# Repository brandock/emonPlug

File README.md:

# emonPlug Overview
OpenEnergyMonitor-compatible energy monitoring US plug. 

emonPlug is an energy monitoring transmitter unit that can monitor AC electrical consumption of one appliance connected to its NEMA 5-15R receptacle. 

emonPlug is designed to be used together with an emonBase web-connected base station from OpenEnergyMonitor. It can be thought of as an emonTx+emonVs for monitoring one appliance.

Make sure to read the warning and disclaimer below before starting any work on emonPlug assembly or use. 

# emonPlug Architecture
emonPlug uses a CT to perform non-invasive current monitoring, similar to emonTx from OpenEnergyMonitor. https://docs.openenergymonitor.org/emontx3/index.html

It uses a voltage transformer for voltage monitoring and includes a built-in power supply, similar to emonVs from OpenEnergyMonitor. https://docs.openenergymonitor.org/emontx4/voltage_sensors.html

It is firmware compatible with emonTx3 (with appropriate calibration settings). emonPlug-specific firmware, based on the emonTx3 firmware, is provided in this repository.

To use emonTx34_CM firmware change the following settings:

float vCal_USA = 111.686;  
float i1Cal = 14.68;                                       
float i1Lead = 7.6;

bool  USA=true;

The emonPlug-specific firmware omits CTs 2, 3, and 4 and provides a more detailed packet for CT1: Vrms, Irms, PowerFactor, Frequency, LogPeriod, RealPower, ApparentPower, WattHours.

# emonPlug Parts
The CT is an AC1015 from Talema Group. It is rated to 15A with 1000:1 turn ratio. https://talema.com/wp-content/uploads/datasheets/AC.pdf

The voltage transformer is the ZMPT101B. This is the same transformer used in the emonVs. The current emonPlug is US-specific, so the 3x10K, 1/4W current-limiting resistors are designed to maximize the waveform of 120V AC. More resistance, more power dissipation, and a different burden resistor would be necessary for anyone modifying emonPlug for use with 240V AC outside the US.

emonPlug uses the Polycase PM2425 AC wall plug enclosure with US 15 AMP 120 VAC plug configuration. https://www.polycase.com/pm2425.

The emonPlug MCU is the Microchip ATMega328 and the radio is the HopeRF RFM69CW, similar to emonTx3.

# emonPlug Photos

# Warning and Disclaimer
Make sure to read this disclaimer before starting any work on emonPlug assembly or use. Credit to Felix Rusu of LowPowerLab for the wise wording of this advice and disclaimer.

emonPlug is isolated from mains electricity via the RECOM PSU (3kV isolation). Additional safety devices in the emonPlug include a current limiting fuse and a MOV (metal oxide varistor) device to help protect against transients.

Electricity WARNING: whenever you touch anything that is or was connected to mains voltages you have to really know what you are doing, otherwise you may shock yourself to shivers. If you are not 100% sure, do yourself a favor and don’t touch anything. ATX power supplies, TVs, CRT/LCD monitors, among most other high voltage devices contain very large capacitors that can hold lethal charges that may or may not discharge after the device is unplugged. You should discharge these caps before touching the circuit.

You should not attempt to assemble or use an emonPlug if you are not familiar with mains wiring! Mains voltage can cause a fatal shock or start a fire when used improperly or negligently! Please consult this electrical safety handbook to understand how you can protect yourself and your equipment from electrical shock.

The emonPlug is not an end consumer product but an open-source design that requires assembly/soldering and is intended for users comfortable/qualified to assemble it. Certain parts are polarized and require proper orientation before soldering otherwise emonPlug may malfunction or not work.
emonPlug also requires programming prior to it being functional. The designer of emonPlug is not liable for how the end user decides to assemble or use and customize the sample firmware code. The information and sample code is meant as an educational resource only, to help guide the end user with assembly and better understand how emonPlug can operate. The end user is fully responsible to ensure the final product will be electrically safe to operate.
Although as a whole, emonPlug is not UL/CSA/CE certified. It uses a certified power supply. However emonPlug comes with NO GUARANTEES expressed or implied and the designer is not liable for any injuries or damage caused by improper assembly or use of emonPlug. It may be against code to install non UL certified equipment in your area, so you are responsible to make sure you are compliant or take any risks on your own. If you do not agree or understand the terms of this disclaimer you should not use emonPlug. Use it at your own risk.

# Alternatives to emonPlug
Switchbot Mini Plug with Tasmota is a good way to monitor energy consumption via emonBase through MQTT. https://templates.blakadder.com/switchbot_plugmini_W1901400.html
The Tasmota firmware can be loaded without disassembling the unit. https://github.com/kendallgoto/switchbota/

Felix Rusu once modified a Kill-a-Watt to transmit readings to an emonBase. https://lowpowerlab.com/tag/arduino/

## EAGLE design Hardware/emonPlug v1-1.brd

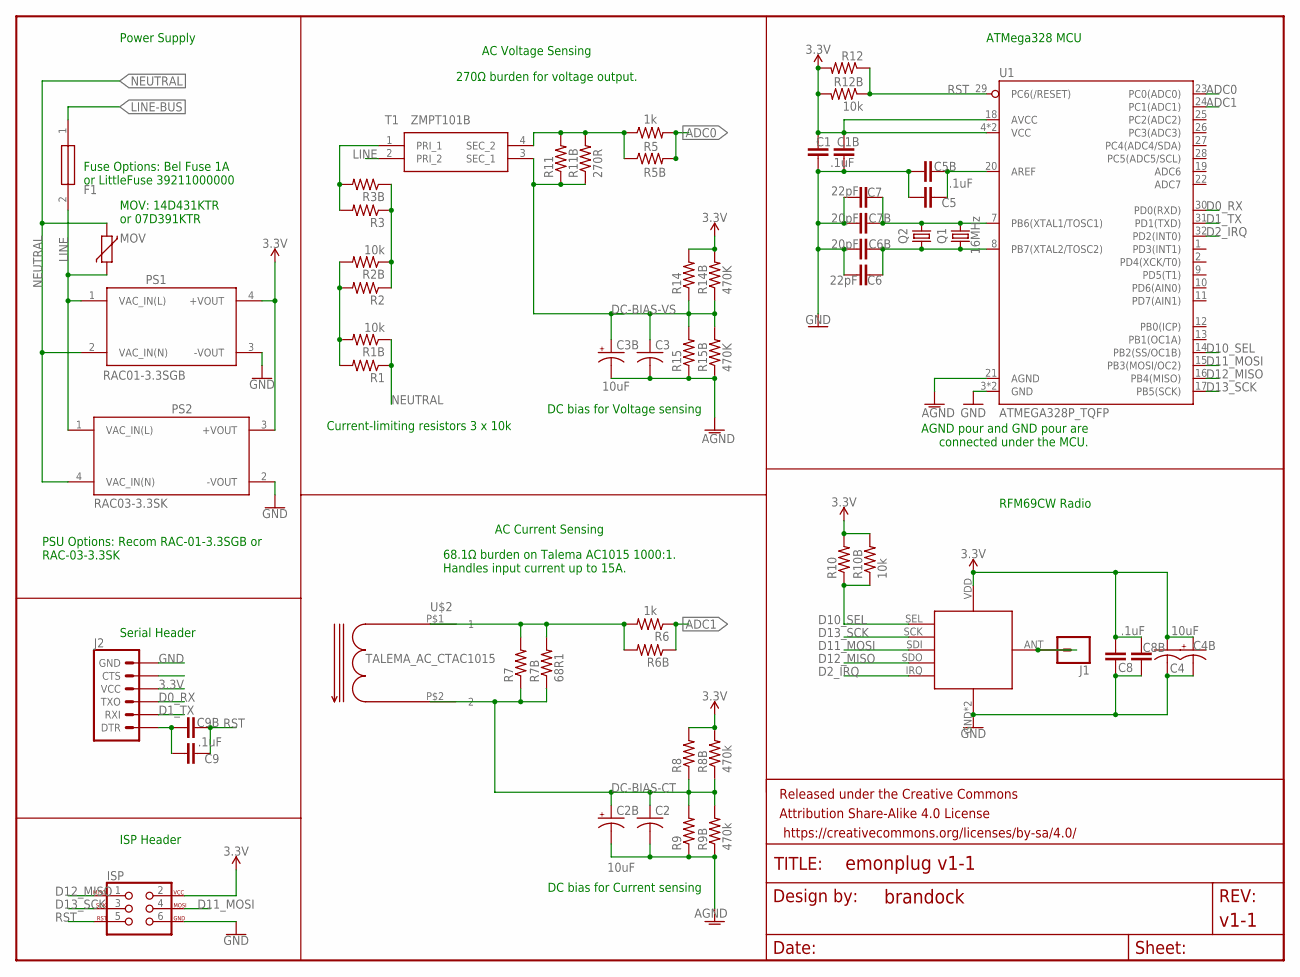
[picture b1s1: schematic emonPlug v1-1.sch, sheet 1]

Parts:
C1, C5, C8, C9: .1uF; C0805
C1B, C5B, C8B, C9B: .1uF; C025-024X044
C2, C3: C-USC0805; C0805
C2B, C3B, C4B: 10uF; E1,8-4
C4: 10uF; C0805
C6, C7: 22pF; C0805
C6B, C7B: 20pF; C025-024X044
F1: 39211000000
FRAME1: FRAME-LETTER; CREATIVE_COMMONS
ISP: AVR_SPI_PROG_3X22X3_LOCK; 2X3_LOCK
J1: CONN_01; 1X01
J2: 6_PIN_SERIAL_TARGET_SILK; 1X06
MOV: VARISTOR-5; R-5
PS1: RAC01-3.3SGB; CONV_RAC01-3.3SGB
PS2: RAC03-3.3SK; CONV_RAC03-3.3SK
Q1: 16MHz; HC49/S-NO-SILK
Q2: CRYSTALHC49UP; HC49UP
R1, R2, R3, R6, R7, R8, R9, R10, R11, R12, R14, R15: R-US_R0805; R0805
R1B, R2B, R10B, R12B: 10k; 0204/7
R3B, R5B: R-US_0204/7; 0204/7
R5: 1k; R0805
R6B: 1k; 0204/7
R7B: 68R1; 0204/7
R8B, R9B: 470k; 0204/7
R11B: 270R; 0204/7
R14B, R15B: 470K; 0204/7
T1: ZMPT101B
U1: ATMEGA328P_TQFP; TQFP32-08
U$2: TALEMA_AC_CTAC1015; AC1005-1020
U$3: RFM12B_MINPADS; RFM12B-MINPADS

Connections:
3.3V: C1.2, C1B.1, C4.1, C4B.+, C8.1, C8B.1, ISP.2, J2.4 (VCC), PS1.4 (+VOUT), PS2.3 (+VOUT), R8.2, R8B.2, R10.2, R10B.2, R12.2, R12B.2, R14.2, R14B.2, U1.4 (VCC), U1.6 (VCC), U1.18 (AVCC), U$3.VDD
ADC0: R5.2, R5B.2, U1.23 (PC0(ADC0))
ADC1: R6.1, R6B.1, U1.24 (PC1(ADC1))
AGND: C2.2, C2B.-, C3.2, C3B.-, R9.1, R9B.1, R15.1, R15B.1, U1.21 (AGND)
D0_RX: J2.3 (TXO), U1.30 (PD0(RXD))
D1_TX: J2.2 (RXI), U1.31 (PD1(TXD))
D2_IRQ: U1.32 (PD2(INT0)), U$3.IRQ
D10_SEL: R10.1, R10B.1, U1.14 (PB2(SS/OC1B)), U$3.SEL
D11_MOSI: ISP.4, U1.15 (PB3(MOSI/OC2)), U$3.SDI (SDI/MOSI)
D12_MISO: ISP.1, U1.16 (PB4(MISO)), U$3.SDO (SDO/MISO)
D13_SCK: ISP.3, U1.17 (PB5(SCK)), U$3.SCK
DC-BIAS-CT: C2.1, C2B.+, R7.1, R7B.1, R8.1, R8B.1, R9.2, R9B.2, U$2.P$2 (2)
DC-BIAS-VS: C3.1, C3B.+, R11.1, R11B.1, R14.1, R14B.1, R15.2, R15B.2, T1.3 (SEC_1)
GND: C1.1, C1B.2, C4.2, C4B.-, C5.1, C5B.1, C6.2, C6B.2, C7.2, C7B.2, C8.2, C8B.2, ISP.6, J2.6 (GND), PS1.3 (-VOUT), PS2.2 (-VOUT), U1.3 (GND), U1.5 (GND), U$3.GND, U$3.GND2 (GND)
LINE: F1.2, MOV.1, PS1.1 (VAC_IN(L)), PS2.1 (VAC_IN(L)), T1.2 (PRI_2)
LINE-BUS: F1.1
unnamed: R6.2, R6B.2, R7.2, R7B.2, U$2.P$1 (1)
unnamed: R3.2, R3B.2, T1.1 (PRI_1)
unnamed: C7.1, C7B.1, Q1.2, Q2.2, U1.7 (PB6(XTAL1/TOSC1))
unnamed: C6.1, C6B.1, Q1.1, Q2.1, U1.8 (PB7(XTAL2/TOSC2))
unnamed: C9.1, C9B.1, J2.1 (DTR)
unnamed: J1.1, U$3.ANT
unnamed: R1.2, R1B.2, R2.2, R2B.2
unnamed: R5.1, R5B.1, R11.2, R11B.2, T1.4 (SEC_2)
unnamed: R2.1, R2B.1, R3.1, R3B.1
unnamed: C5.2, C5B.2, U1.20 (AREF)
NEUTRAL: MOV.2, PS1.2 (VAC_IN(N)), PS2.4 (VAC_IN(N)), R1.1, R1B.1
RST: C9.2, C9B.2, ISP.5, R12.1, R12B.1, U1.29 (PC6(/RESET))

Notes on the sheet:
RFM69CW Radio
ATMega328 MCU
DC bias for Voltage sensing
270Ω burden for voltage output.
Current-limiting resistors 3 x 10k
AC Voltage Sensing
68.1Ω burden on Talema AC1015 1000:1. Handles input current up to 15A.
AC Current Sensing
Fuse Options: Bel Fuse 1A or LittleFuse 39211000000
MOV: 14D431KTR or 07D391KTR
PSU Options: Recom RAC-01-3.3SGB or RAC-03-3.3SK
Power Supply
DC bias for Current sensing
Serial Header
ISP Header
AGND pour and GND pour are connected under the MCU.

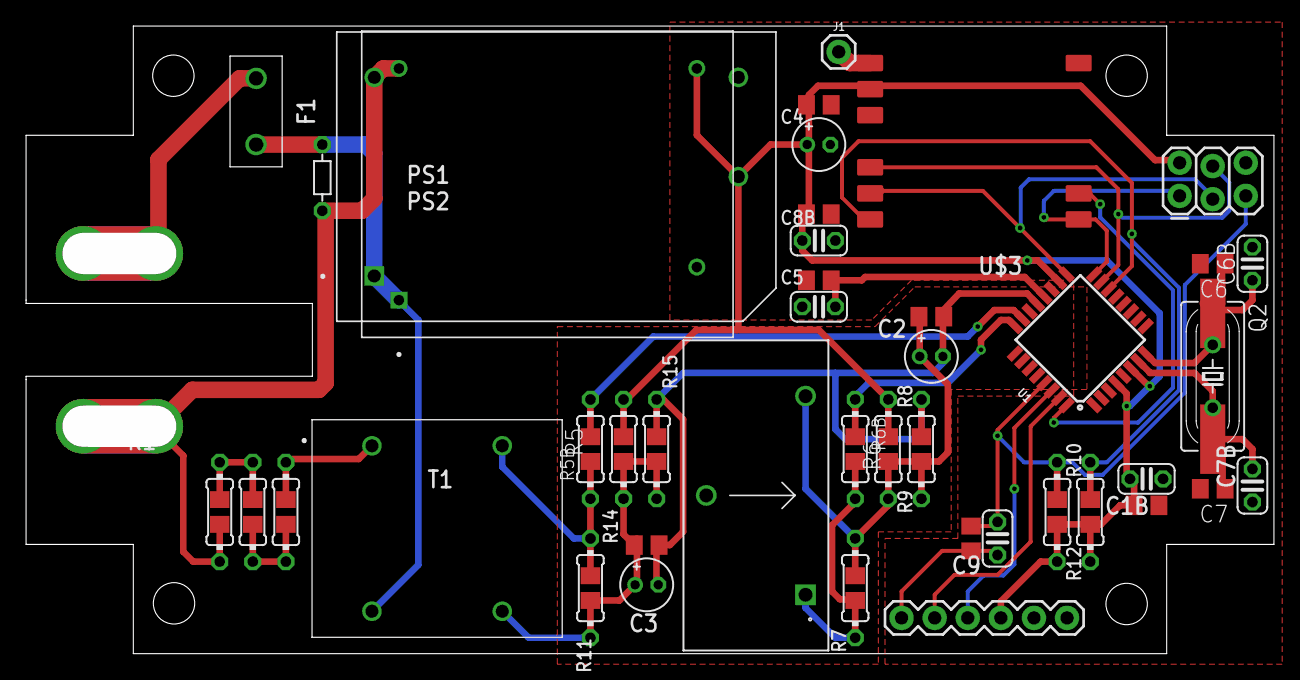
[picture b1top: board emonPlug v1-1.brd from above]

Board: 2 copper layers, 92.6 x 45.0 mm, 58 parts (0 on the bottom side), 27 nets.

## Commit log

2020-12-14 Create Firmware
2023-08-26 Add Firmware directory
2023-08-26 Add Hardware directory
2023-08-27 Add bill of materials

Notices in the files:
parts and their libraries:
SparkFun-Aesthetics: Licensing: Creative Commons ShareAlike 4.0 International - https://creativecommons.org/licenses/by-sa/4.0
SparkFun-Aesthetics: Released under the Creative Commons Attribution Share-Alike 4.0 License
SparkFun-Aesthetics: https://creativecommons.org/licenses/by-sa/4.0
